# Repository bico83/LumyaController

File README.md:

# LumyaController
HW/SW project for lumya illumination

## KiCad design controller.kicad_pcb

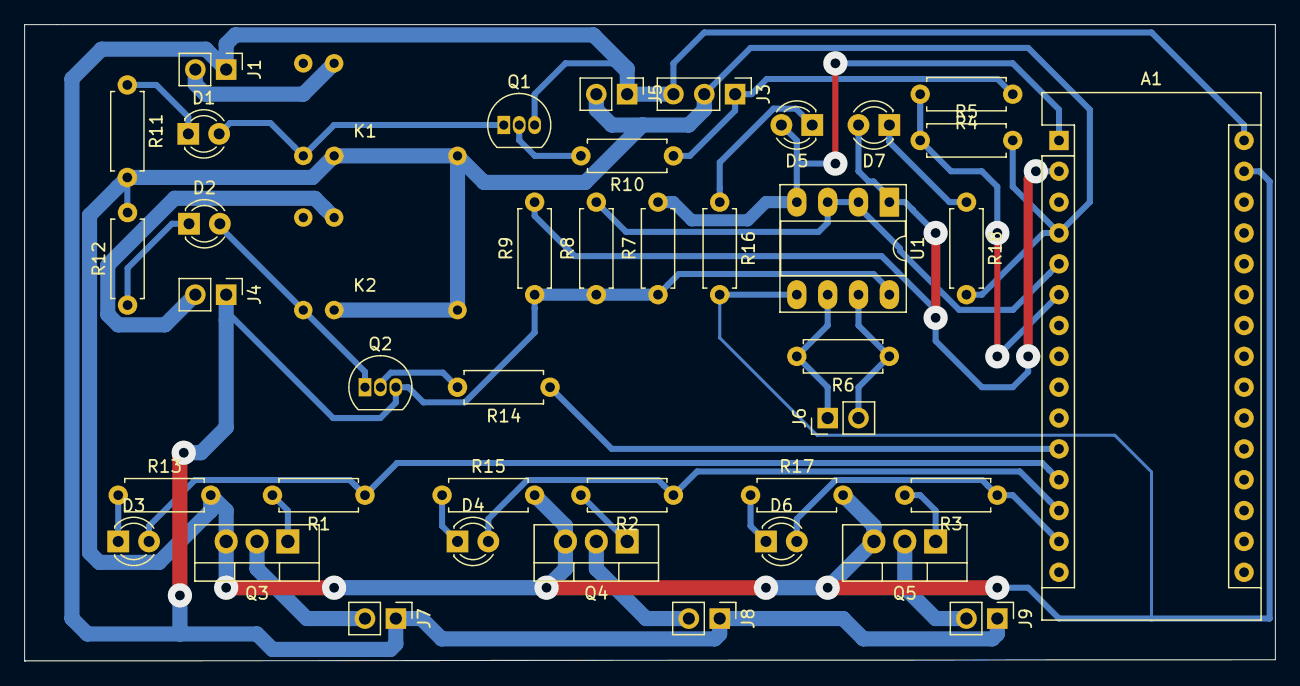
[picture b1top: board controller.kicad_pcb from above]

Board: 2 copper layers, 103.0 x 52.4 mm, 42 parts (0 on the bottom side), 32 nets.

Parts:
A1: Arduino_Nano_v3.x; Arduino_Nano
D1, D2, D3, D4, D5, D6, D7: LED; LED_D3.0mm
J1, J4, J6, J7, J8, J9: Conn_01x02; PinHeader_1x02_P2.54mm_Vertical
J3: Conn_01x03_Female; PinHeader_1x03_P2.54mm_Vertical
J5: Conn_01x02_Male; PinHeader_1x02_P2.54mm_Vertical
K1, K2: steren-relay
Q1, Q2: PN2222A; TO-92_Inline
Q3, Q4, Q5: IRF740; TO-220-3_Vertical
R1, R2, R3, R4, R5, R6: R; R_Axial_DIN0207_L6.3mm_D2.5mm_P7.62mm_Horizontal
R7, R8, R9: 10K; R_Axial_DIN0207_L6.3mm_D2.5mm_P7.62mm_Horizontal
R10, R11, R12, R13, R14, R15, R16, R17, R18: 1K; R_Axial_DIN0207_L6.3mm_D2.5mm_P7.62mm_Horizontal
U1: MAX485E; DIP-8_W7.62mm_Socket_LongPads

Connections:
GND: A1.4, A1.29, J3.2, J5.2, K1.4, K1.5, K2.4, K2.5, Q3.3, Q4.3, Q5.3, R5.2, R11.2, R12.2, R13.2, R15.2, R16.2, R17.2, R18.2, U1.5
unnamed: A1.1, D5.2, R7.2, U1.4
unnamed: A1.2, D7.2, R9.2, U1.1
unnamed: A1.5, R8.2, U1.2, U1.3
unnamed: A1.6, R4.2, R5.1
unnamed: A1.11, R14.1
unnamed: A1.12, D3.2, R1.1
unnamed: A1.13, D4.2, R2.1
unnamed: A1.14, D6.2, R3.1
unnamed: D1.1, R11.1
unnamed: D1.2, K1.2, Q1.1
unnamed: D2.1, R12.1
unnamed: D2.2, K2.2, Q2.1
unnamed: D3.1, R13.1
unnamed: D4.1, R15.1
unnamed: D5.1, R16.1
unnamed: D6.1, R17.1
unnamed: D7.1, R18.1
unnamed: J1.2, K1.3
unnamed: J3.1, R4.1, R10.1
unnamed: J4.2, K2.3
unnamed: J6.1, R6.2, U1.6
unnamed: J6.2, R6.1, U1.7
unnamed: J7.2, Q3.2
unnamed: J8.2, Q4.2
unnamed: J9.2, Q5.2
unnamed: Q1.2, R10.2
unnamed: Q2.2, R14.2
unnamed: Q3.1, R1.2
unnamed: Q4.1, R2.2
unnamed: Q5.1, R3.2
VCC: A1.30, J1.1, J3.3, J4.1, J5.1, J7.1, J8.1, J9.1, Q1.3, Q2.3, R7.1, R8.1, R9.1, U1.8

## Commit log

2020-02-19 Added max485 and power circuitry
2020-02-20 Routed PCB with test components
2020-02-20 Added relays symbol and footprint. Re-routed|
